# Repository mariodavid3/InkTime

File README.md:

# David Adrian-Mario

## Overview

Acest proiect consta intr-un dispozitiv embedded portabil bazat pe **nRF52840**, capabil sa controleze un display **E-Paper**, sa colecteze date de la un **IMU**, sa ofere feedback prin **haptic driver**, si sa functioneze autonom pe baterie Li-Po.

Dispozitivul include:

* alimentare Li-Po + incarcare USB-C
* conversie DC/DC
* control display e-paper
* senzor IMU
* fuel gauge pentru baterie
* interfata utilizator (butoane + vibratii)
* debugging prin SWD

---
## Materiale

## Block Diagram

## Functionalitate Hardware

### Alimentare

* Intrare: USB-C (5V)
* incarcare baterie Li-Po prin IC dedicat
* Fuel gauge monitorizeaza:
  
  * tensiune
  * nivel baterie
  * estimare autonomie

### DC/DC

* Conversie de la baterie (~3.7V) la 3.3V stabil
* Alimentare pentru MCU si periferice
* Optimizat pentru consum redus

---

### MCU – nRF52840

Roluri:

* control general sistem
* comunicare I2C/SPI
* control display e-paper
* citire senzori
* BLE (optional)

---

### E-Paper

* Controlat prin SPI
* Necesita:

  * tensiuni multiple generate de circuit dedicat (boost + diode)
* Avantaj:

  * consum foarte mic (doar la refresh)

---

### IMU

* Conectat pe I2C
* Masoara:

  * acceleratie
  * rotatie

---

### Haptic

* Driver dedicat (DRV2605)
* Control prin I2C
* Feedback tactil pentru UI

---

### Butoane

* 3 butoane:

  * UP
  * DOWN
  * ENTER
* Conectate la GPIO
* Pull-up/pull-down hardware

---
### USB + ESD

* USB-C pentru alimentare
* Protectie ESD pentru:

  * D+
  * D-
  * VBUS

---

### SWD

* Interfata debugging:

  * SWDIO
  * SWCLK
  * RESET

---

## Mapare pini nRF52840

| Functie        | Pin MCU | Motiv                |
| -------------- | ------- | -------------------- |
| SPI E-Paper    | P0.x    | viteza mare necesara |
| I2C IMU        | P0.x    | standard I2C         |
| I2C Fuel Gauge | P0.x    | bus comun            |
| I2C Haptic     | P0.x    | bus comun            |
| Buttons        | P0.x    | GPIO simplu          |
| SWDIO          | dedicat | debugging            |
| SWCLK          | dedicat | debugging            |
| RESET          | dedicat | control              |

**Motivatie design:**

* I2C shared → reduce pini
* SPI separat → performanta display
* GPIO dedicate → simplitate

---

## Consum de energie (estimare)

| Modul           | Consum           |
| --------------- | ---------------- |
| MCU activ       | ~5-10 mA         |
| MCU sleep       | <10 µA           |
| E-paper refresh | 20-50 mA (scurt) |
| IMU             | ~1-3 mA          |
| Haptic          | ~100 mA (peak)   |

### Optimizari:

* sleep mode agresiv
* e-paper doar la update
* oprire periferice nefolosite

---

## Design PCB

### Observatii:

* Layout compact, dens
* Separare:

  * analog (power)
  * digital (MCU)
* Ground plane continuu
* Trasee scurte pentru:

  * SPI
  * I2C

### Consideratii:

* decuplare langa fiecare IC
* trasee groase pentru power
* protectie ESD langa conector

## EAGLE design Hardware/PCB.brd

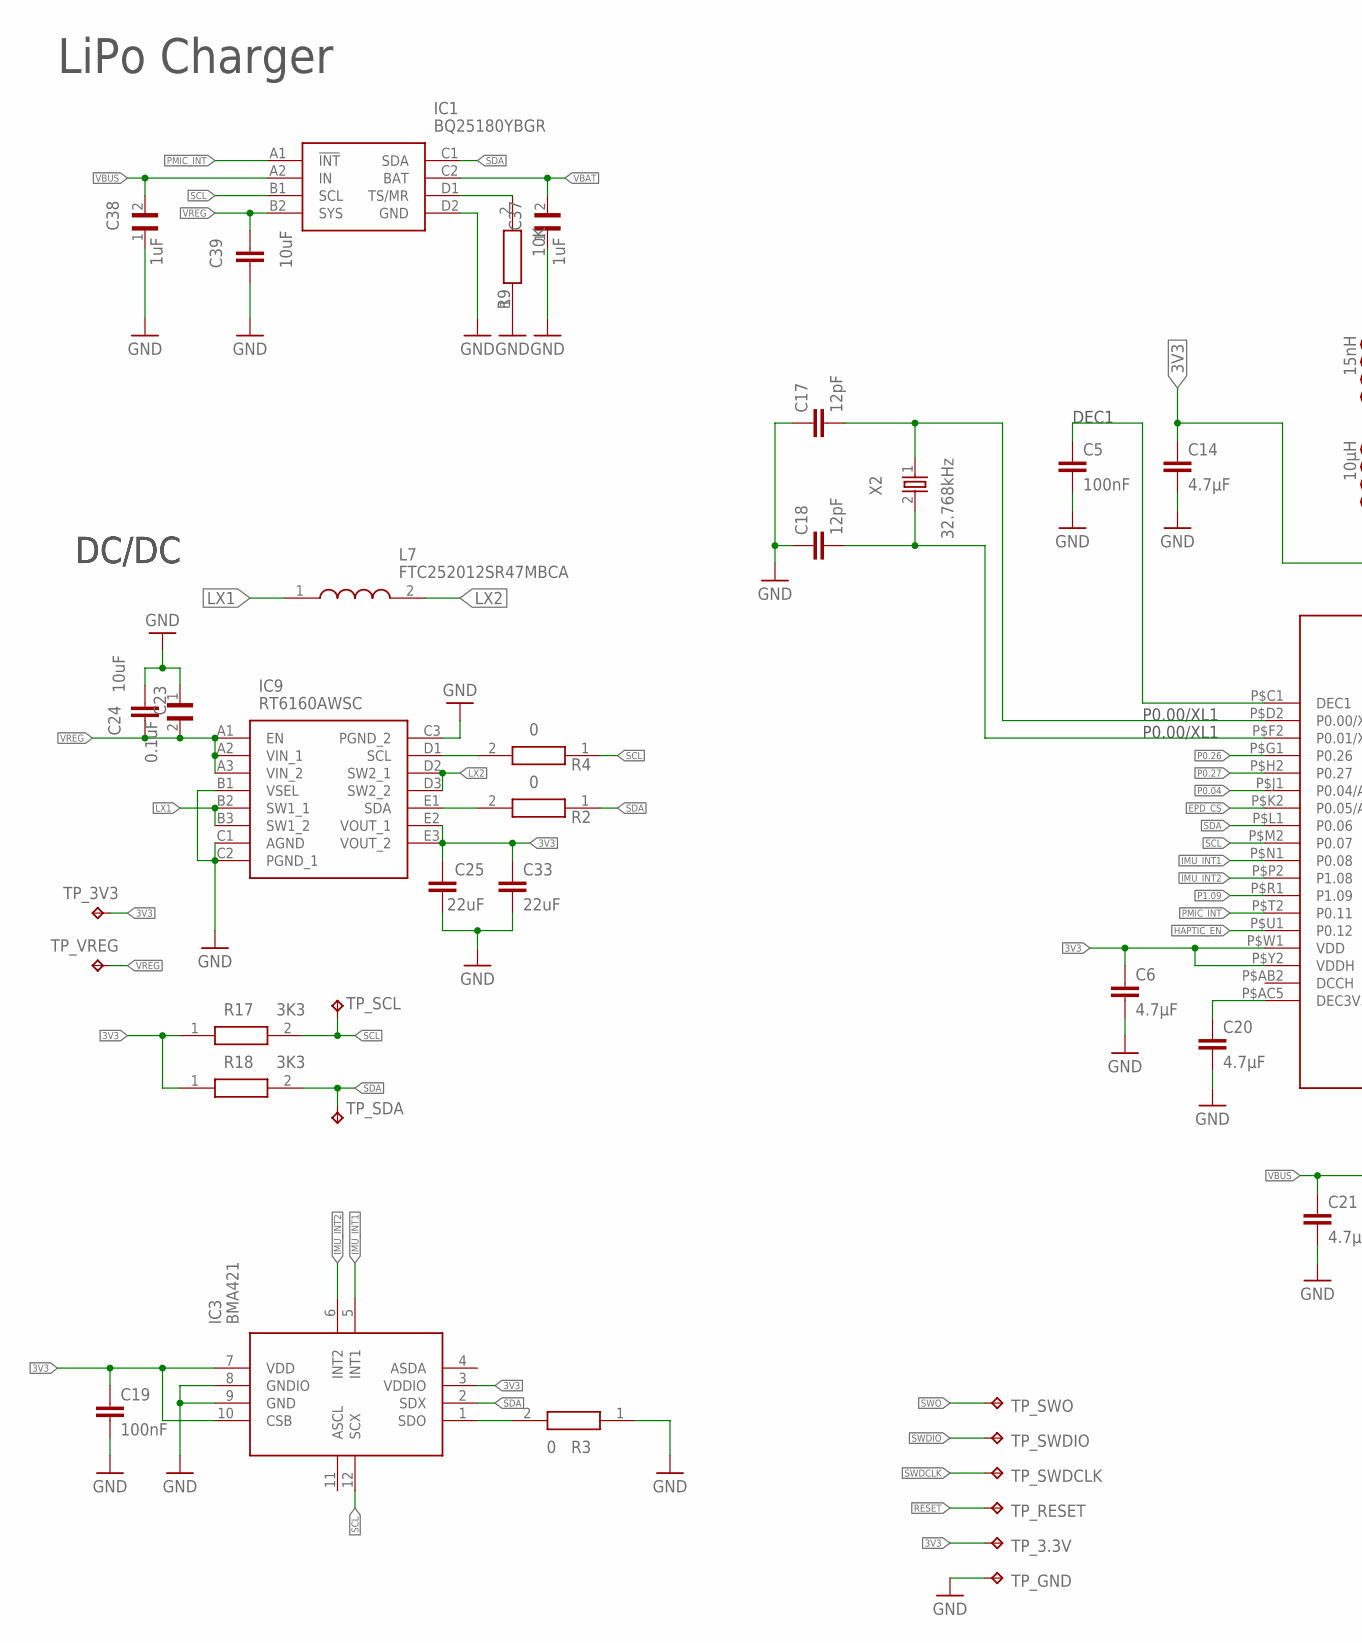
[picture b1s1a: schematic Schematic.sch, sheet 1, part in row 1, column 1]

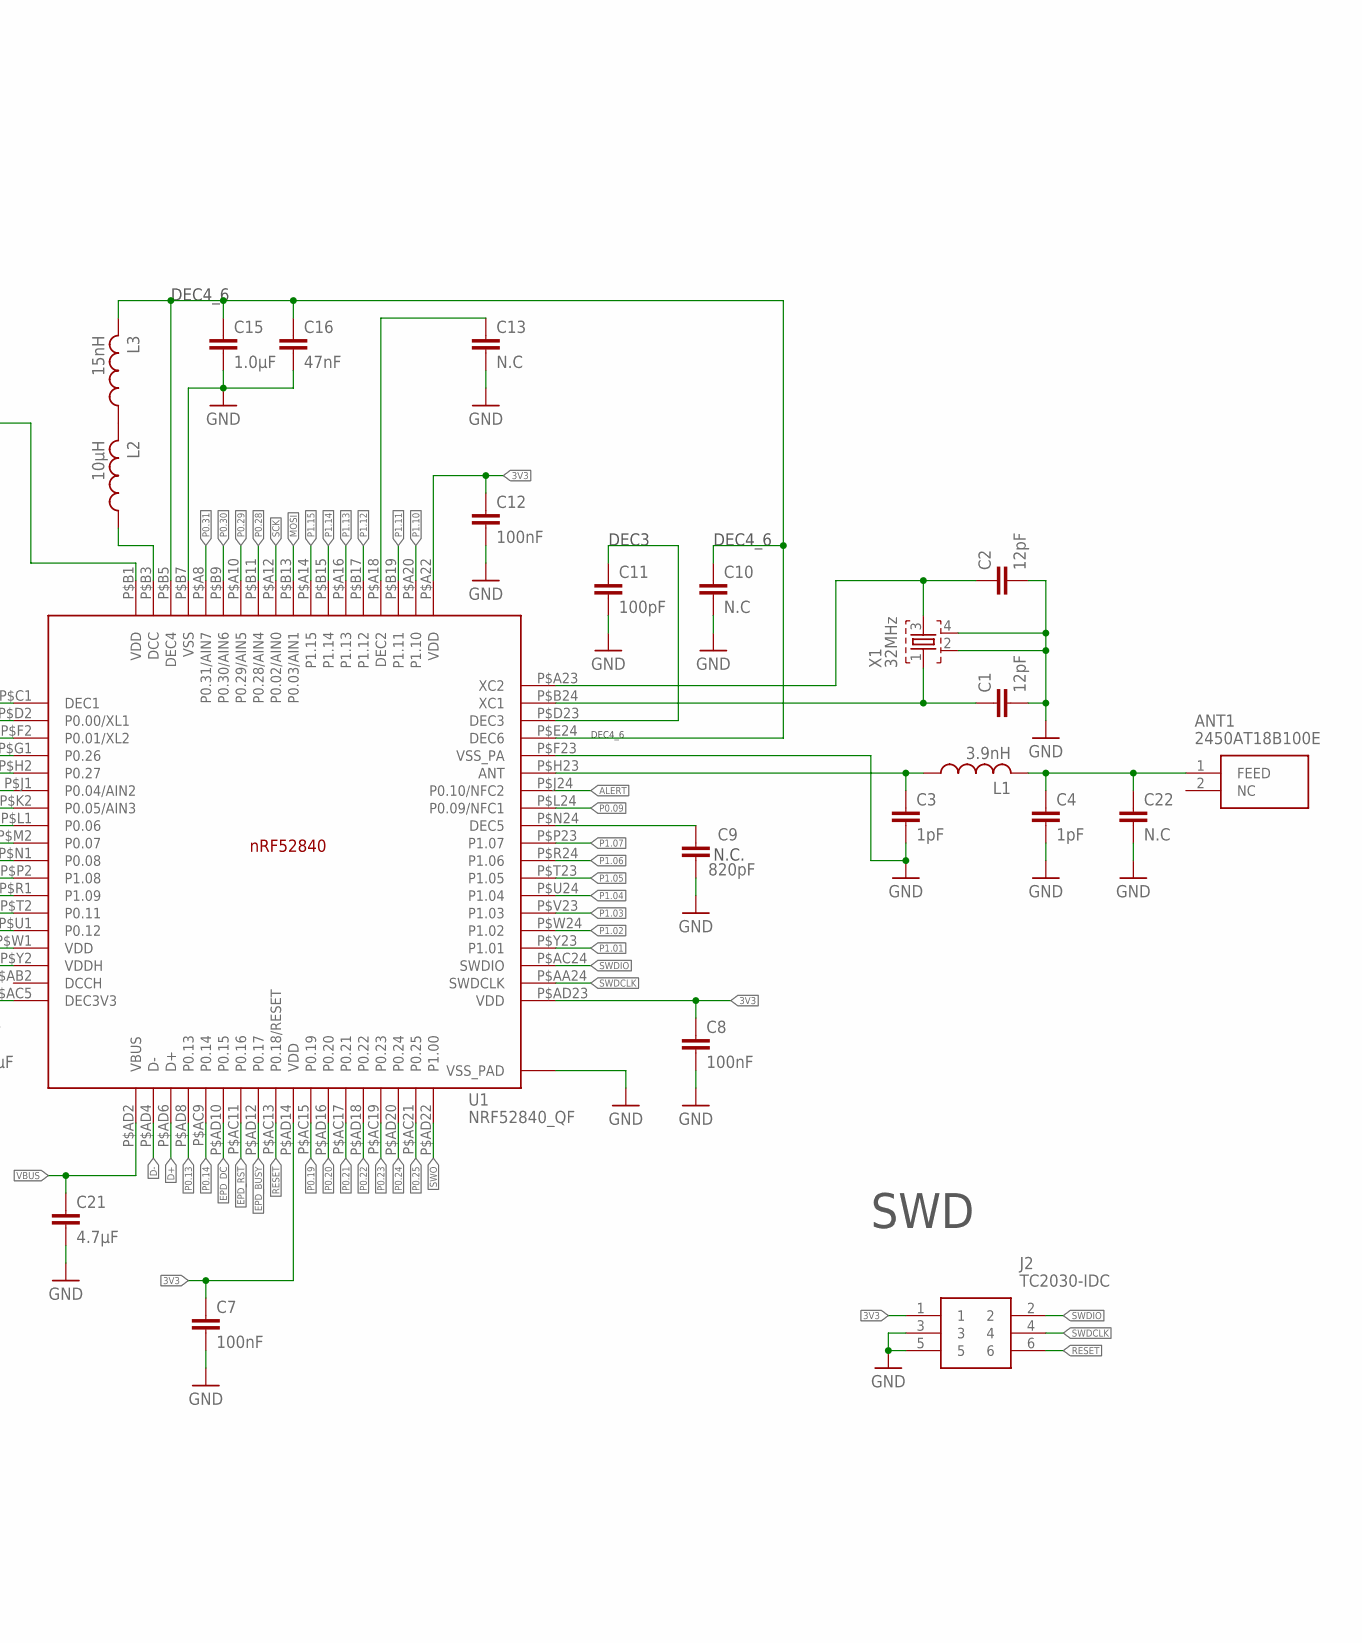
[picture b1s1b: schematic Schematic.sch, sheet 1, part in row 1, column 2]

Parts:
ANT1: 2450AT18B100E; 2450AT18B100E_ANTC3216X140N
C1, C2, C17, C18: 12pF; NORDIC_NRF_3_RESC0201_L
C3, C4: 1pF; NORDIC_NRF_3_RESC0201_L
C5, C7, C8, C12, C19: 100nF; NORDIC_NRF_3_RESC0201_L
C6, C14, C20, C21: 4.7µF; PERFECT_0402_0402
C9: 820pF; NORDIC_NRF_3_RESC0201_L
C10, C13, C22: N.C; NORDIC_NRF_3_RESC0201_L
C11: 100pF; NORDIC_NRF_3_RESC0201_L
C15: 1.0µF; PERFECT_0402_0402
C16: 47nF; NORDIC_NRF_3_RESC0201_L
C23: 0.1uF; GRM011R60J152KE01L_2_CAPC0201X13N
C24, C39: 10uF; PERFECT_0402_0402
C25, C33: 22uF; PERFECT_0402_0402
C37, C38: 1uF; GRM011R60J152KE01L_2_CAPC0201X13N
IC1: BQ25180YBGR; BQ25180YBGR_BGA8C40P2X4_100X155X50
IC3: BMA421; BMA423_BMA423
IC9: RT6160AWSC; RT6160AWSC_BGA15C40P3X5_140X230X60
J2: TC2030-IDC; TC2030-IDC_TC2030IDC
L1: 3.9nH; NORDIC_NRF_2_RESC0402_L
L2: 10µH; NORDIC_NRF_2_RESC0402_L
L3: 15nH; NORDIC_NRF_2_RESC0402_L
L7: FTC252012SR47MBCA; MLP2016SR47MT0S1_INDC2016X100N
R2, R3, R4: 0; CPF0201D7K68C1_0201
R9: 10K; CPF0201D7K68C1_0201
R17, R18: 3K3; CPF0201D7K68C1_0201
TP_3.3V, TP_3V3: HECTOR_WATCH_1_TPTP20R; HECTOR_WATCH_1_TP20R
TP_GND: HECTOR_WATCH_1_TPTP20R; HECTOR_WATCH_1_TP20R
TP_RESET: HECTOR_WATCH_1_TPTP20R; HECTOR_WATCH_1_TP20R
TP_SCL: HECTOR_WATCH_1_TPTP20R; HECTOR_WATCH_1_TP20R
TP_SDA: HECTOR_WATCH_1_TPTP20R; HECTOR_WATCH_1_TP20R
TP_SWDCLK: HECTOR_WATCH_1_TPTP20R; HECTOR_WATCH_1_TP20R
TP_SWDIO: HECTOR_WATCH_1_TPTP20R; HECTOR_WATCH_1_TP20R
TP_SWO: HECTOR_WATCH_1_TPTP20R; HECTOR_WATCH_1_TP20R
TP_VREG: HECTOR_WATCH_1_TPTP20R; HECTOR_WATCH_1_TP20R
U1: NRF52840_QF; NORDIC_NRF_4_AQFN50P700X700X85_HS-74N
X1: 32MHz; NORDIC_NRF_BT-XTAL_2016_N
X2: 32.768kHz; NORDIC_NRF_1_XTAL_3215_N

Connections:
3V3: C6.1, C7.1, C8.1, C12.1, C14.1, C19.1, C25.2, C33.1, IC3.3 (VDDIO), IC3.7 (VDD), IC3.10 (CSB), IC9.E2 (VOUT_1), IC9.E3 (VOUT_2), J2.1, R17.1, R18.1, TP_3.3V.TP, TP_3V3.TP, U1.P$A22 (VDD), U1.P$AD14 (VDD), U1.P$AD23 (VDD), U1.P$B1 (VDD), U1.P$W1 (VDD), U1.P$Y2 (VDDH); also elsewhere on the board
ALERT: U1.P$J24 (P0.10/NFC2); also elsewhere on the board
D+: U1.P$AD6 (D+); also elsewhere on the board
D-: U1.P$AD4 (D-); also elsewhere on the board
EPD_BUSY: U1.P$AD12 (P0.17); also elsewhere on the board
EPD_CS: U1.P$K2 (P0.05/AIN3); also elsewhere on the board
EPD_DC: U1.P$AD10 (P0.15); also elsewhere on the board
EPD_RST: U1.P$AC11 (P0.16); also elsewhere on the board
GND: C1.2, C2.2, C3.2, C4.2, C5.2, C6.2, C7.2, C8.2, C9.1, C10.2, C11.2, C12.2, C13.2, C14.2, C15.2, C16.2, C17.1, C18.1, C19.2, C20.2, C21.2, C22.2, C23.1, C24.1, C25.1, C33.2, C37.1, C38.1, C39.1, IC1.D2 (GND), IC3.8 (GNDIO), IC3.9 (GND), IC9.B1 (VSEL), IC9.C1 (AGND), IC9.C2 (PGND_1), IC9.C3 (PGND_2), J2.3, J2.5, R3.1, R9.1, TP_GND.TP, U1.P$74 (VSS_PAD), U1.P$75 (VSS_PAD), U1.P$76 (VSS_PAD), U1.P$77 (VSS_PAD), U1.P$78 (VSS_PAD), U1.P$79 (VSS_PAD), U1.P$80 (VSS_PAD), U1.P$81 (VSS_PAD), U1.P$82 (VSS_PAD), U1.P$83 (VSS_PAD), U1.P$84 (VSS_PAD), U1.P$85 (VSS_PAD), U1.P$86 (VSS_PAD), U1.P$87 (VSS_PAD), U1.P$88 (VSS_PAD), U1.P$89 (VSS_PAD), U1.P$90 (VSS_PAD), U1.P$B7 (VSS), U1.P$F23 (VSS_PA), X1.2, X1.4; also elsewhere on the board
HAPTIC_EN: U1.P$U1 (P0.12); also elsewhere on the board
IMU_INT1: IC3.5 (INT1), U1.P$N1 (P0.08)
IMU_INT2: IC3.6 (INT2), U1.P$P2 (P1.08)
LX1: IC9.B2 (SW1_1), IC9.B3 (SW1_2), L7.1
LX2: IC9.D2 (SW2_1), IC9.D3 (SW2_2), L7.2
MOSI: U1.P$B13 (P0.03/AIN1); also elsewhere on the board
unnamed: IC1.D1 (TS/MR), R9.2
unnamed: IC3.1 (SDO), R3.2
unnamed: IC9.D1 (SCL), R4.2
unnamed: C9.2, U1.P$N24 (DEC5)
unnamed: IC9.E1 (SDA), R2.2
unnamed: C20.1, U1.P$AC5 (DEC3V3)
unnamed: C13.1, U1.P$A18 (DEC2)
unnamed: C11.1, U1.P$D23 (DEC3)
unnamed: L2.1, U1.P$B3 (DCC)
unnamed: L2.2, L3.1
unnamed: C10.1, C15.1, C16.1, L3.2, U1.P$B5 (DEC4), U1.P$E24 (DEC6)
unnamed: C2.1, U1.P$A23 (XC2), X1.3
unnamed: C1.1, U1.P$B24 (XC1), X1.1
unnamed: C3.1, L1.1, U1.P$H23 (ANT)
unnamed: ANT1.1 (FEED), C4.1, C22.1, L1.2
unnamed: C18.2, U1.P$F2 (P0.01/XL2), X2.2
unnamed: C17.2, U1.P$D2 (P0.00/XL1), X2.1
unnamed: C5.1, U1.P$C1 (DEC1)
P0.04: U1.P$J1 (P0.04/AIN2)
P0.09: U1.P$L24 (P0.09/NFC1)
P0.13: U1.P$AD8 (P0.13); also elsewhere on the board
P0.14: U1.P$AC9 (P0.14); also elsewhere on the board
P0.19: U1.P$AC15 (P0.19)
P0.20: U1.P$AD16 (P0.20)
P0.21: U1.P$AC17 (P0.21)
P0.22: U1.P$AD18 (P0.22)
P0.23: U1.P$AC19 (P0.23)
P0.24: U1.P$AD20 (P0.24)
P0.25: U1.P$AC21 (P0.25)
P0.26: U1.P$G1 (P0.26)
P0.27: U1.P$H2 (P0.27)
P0.28: U1.P$B11 (P0.28/AIN4)
P0.29: U1.P$A10 (P0.29/AIN5)
P0.30: U1.P$B9 (P0.30/AIN6)
P0.31: U1.P$A8 (P0.31/AIN7)
P1.01: U1.P$Y23 (P1.01); also elsewhere on the board
P1.02: U1.P$W24 (P1.02); also elsewhere on the board
P1.03: U1.P$V23 (P1.03)
P1.04: U1.P$U24 (P1.04)
P1.05: U1.P$T23 (P1.05)
P1.06: U1.P$R24 (P1.06)
P1.07: U1.P$P23 (P1.07)
P1.09: U1.P$R1 (P1.09)
P1.10: U1.P$A20 (P1.10)
P1.11: U1.P$B19 (P1.11)
P1.12: U1.P$B17 (P1.12)
P1.13: U1.P$A16 (P1.13)
P1.14: U1.P$B15 (P1.14)
P1.15: U1.P$A14 (P1.15)
PMIC_INT: IC1.A1 (!INT), U1.P$T2 (P0.11)
RESET: J2.6, TP_RESET.TP, U1.P$AC13 (P0.18/RESET)
SCK: U1.P$A12 (P0.02/AIN0); also elsewhere on the board
SCL: IC1.B1 (SCL), IC3.12 (SCX), R4.1, R17.2, TP_SCL.TP, U1.P$M2 (P0.07); also elsewhere on the board
SDA: IC1.C1 (SDA), IC3.2 (SDX), R2.1, R18.2, TP_SDA.TP, U1.P$L1 (P0.06); also elsewhere on the board
SWDCLK: J2.4, TP_SWDCLK.TP, U1.P$AA24 (SWDCLK)
SWDIO: J2.2, TP_SWDIO.TP, U1.P$AC24 (SWDIO)
SWO: TP_SWO.TP, U1.P$AD22 (P1.00)
VBAT: C37.2, IC1.C2 (BAT); also elsewhere on the board
VBUS: C21.1, C38.2, IC1.A2 (IN), U1.P$AD2 (VBUS); also elsewhere on the board
VREG: C23.2, C24.2, C39.2, IC1.B2 (SYS), IC9.A1 (EN), IC9.A2 (VIN_1), IC9.A3 (VIN_2), TP_VREG.TP

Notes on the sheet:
LiPo Charger
DC/DC
SWD
P0.00/XL1
DEC4_6
DEC1
DEC3
N.C.

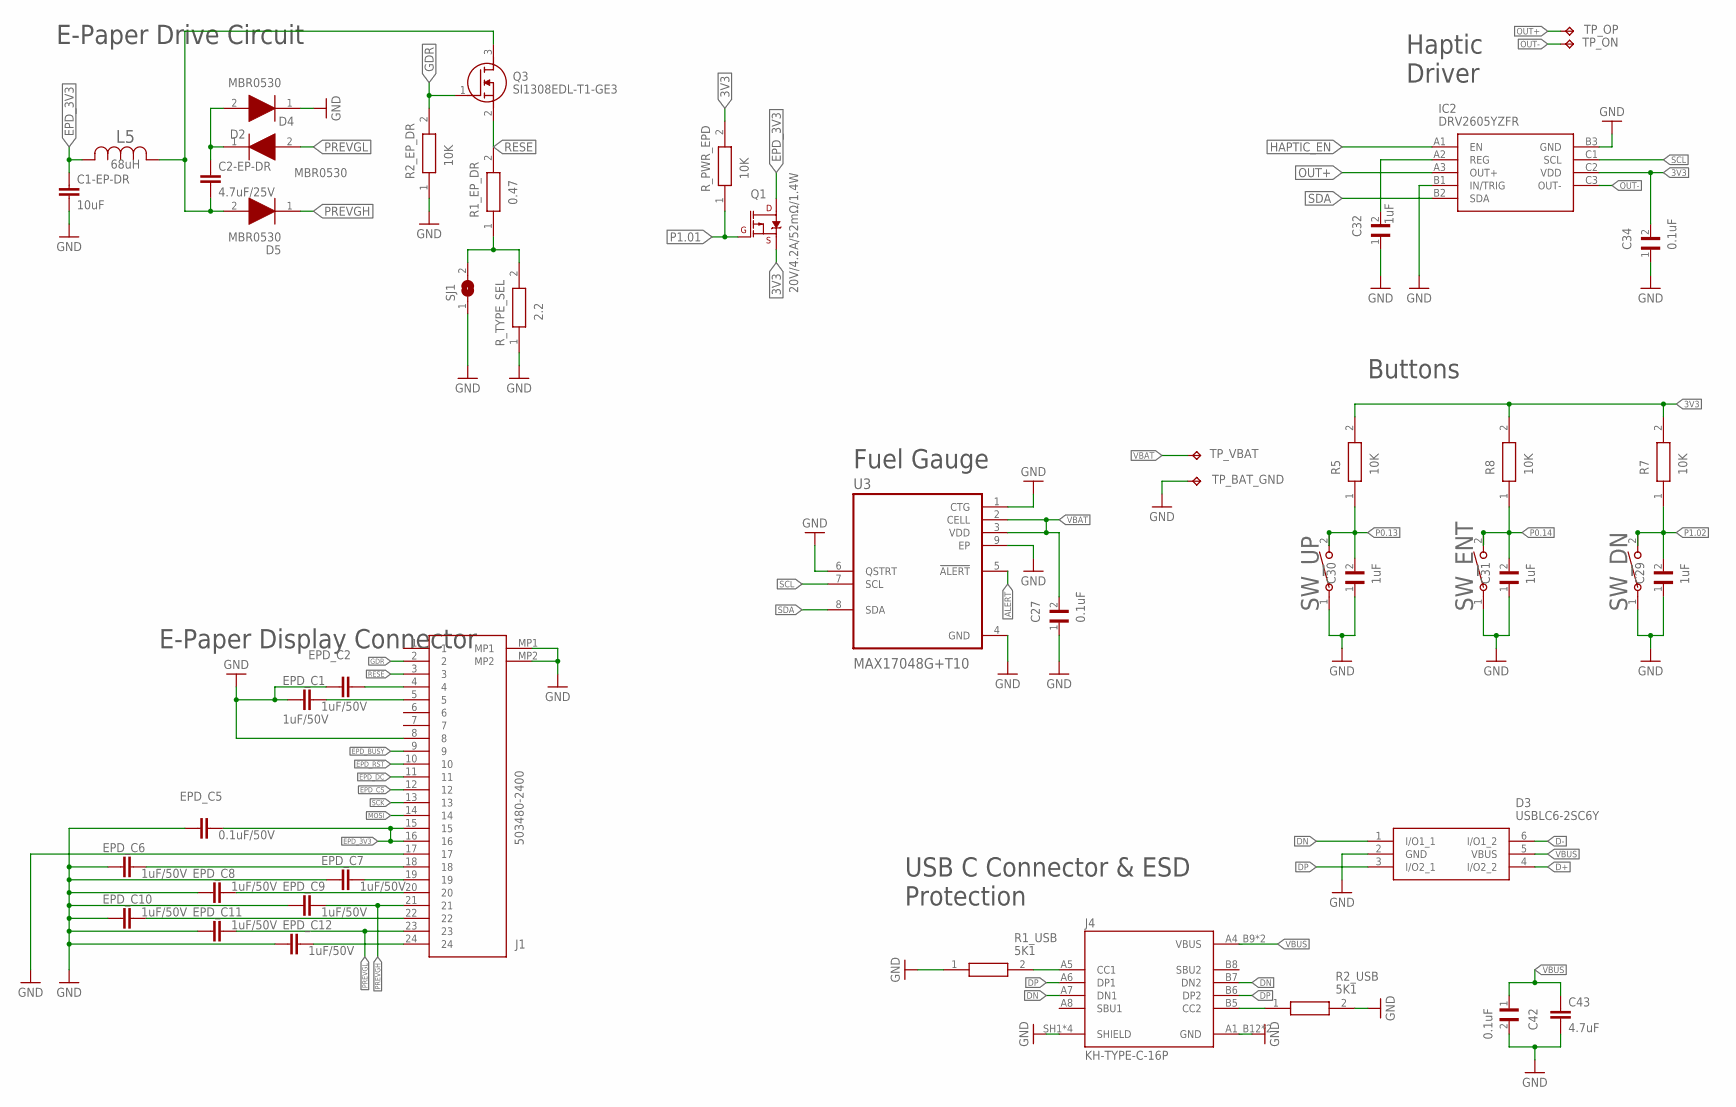
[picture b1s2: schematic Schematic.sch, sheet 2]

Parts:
C1-EP-DR: 10uF; NORDIC_NRF_3_RESC0603_L
C2-EP-DR: 4.7uF/25V; NORDIC_NRF_3_RESC0603_L
C27, C34, C42: 0.1uF; GRM011R60J152KE01L_2_CAPC0201X13N
C29, C30, C31, C32: 1uF; GRM011R60J152KE01L_2_CAPC0201X13N
C43: 4.7uF; PERFECT_0402_0402
D2, D4, D5: MBR0530; ESP32_C6_LIBRARY_5_SOD3716X135N
D3: USBLC6-2SC6Y; ESP32_C6_LIBRARY_3_SOT95P280X145-6N
EPD_C1, EPD_C2, EPD_C6, EPD_C7, EPD_C8, EPD_C9, EPD_C10, EPD_C11, EPD_C12: 1uF/50V; PERFECT_0402_0402
EPD_C5: 0.1uF/50V; NORDIC_NRF_3_RESC0201_L
IC2: DRV2605YZFR; DRV2605YZFR_BGA9C50P3X3_144X144X62
J1: 503480-2400; 503480-2400_5034802400
J4: KH-TYPE-C-16P; KH-TYPE-C-16P_KINGHELM_KH-TYPE-C-16P
L5: 68uH; ESP32_C6_LIBRARY_2_IND_4828-WE-TPC_WRE
Q1: 20V/4.2A/52mΩ/1.4W; ESP32_C6_LIBRARY_4_ESP32_C6_LIBRARY_4_ESP32_C6_LIBRARY_4_ES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
Q3: SI1308EDL-T1-GE3; ESP32_C6_LIBRARY_6_SOT65P210X110-3N
R1_EP_DR: 0.47; CPF0201D7K68C1_0201
R1_USB, R2_USB: 5K1; CPF0201D7K68C1_0201
R2_EP_DR, R5, R7, R8: 10K; CPF0201D7K68C1_0201
R_PWR_EPD: 10K; CPF0201D7K68C1_0201
R_TYPE_SEL: 2.2; CPF0201D7K68C1_0201
SJ1: ESP32_C6_LIBRARY_7_JUMPER_SJ
SW_DN: 2025-10-22_07-23-44_LIBRARY_EVP-AKE31ASW_EVP-AKE3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; 2025-10-22_07-23-44_LIBRARY_SW_EVP-AKE31A_PAN
SW_ENT: 2025-10-22_07-23-44_LIBRARY_EVP-AKE31ASW_EVP-AKE3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; 2025-10-22_07-23-44_LIBRARY_SW_EVP-AKE31A_PAN
SW_UP: 2025-10-22_07-23-44_LIBRARY_EVP-AKE31ASW_EVP-AKE3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; 2025-10-22_07-23-44_LIBRARY_SW_EVP-AKE31A_PAN
TP_BAT_GND: HECTOR_WATCH_1_TPTP20R; HECTOR_WATCH_1_TP20R
TP_ON: HECTOR_WATCH_1_TPTP20R; HECTOR_WATCH_1_TP20R
TP_OP: HECTOR_WATCH_1_TPTP20R; HECTOR_WATCH_1_TP20R
TP_VBAT: HECTOR_WATCH_1_TPTP20R; HECTOR_WATCH_1_TP20R
U3: MAX17048G+T10; ESP32_C6_LIBRARY_SON50P200X200X80-9N

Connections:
3V3: C34.2, IC2.C2 (VDD), Q1.2 (S), R5.2, R7.2, R8.2, R_PWR_EPD.2; also elsewhere on the board
ALERT: U3.5 (!ALERT); also elsewhere on the board
D+: D3.4 (I/O2_2); also elsewhere on the board
D-: D3.6 (I/O1_2); also elsewhere on the board
DN: D3.1 (I/O1_1), J4.A7 (DN1), J4.B7 (DN2)
DP: D3.3 (I/O2_1), J4.A6 (DP1), J4.B6 (DP2)
EPD_3V3: C1-EP-DR.1, EPD_C5.1, J1.15, J1.16, L5.2, Q1.3 (D)
EPD_BUSY: J1.9; also elsewhere on the board
EPD_CS: J1.12; also elsewhere on the board
EPD_DC: J1.11; also elsewhere on the board
EPD_RST: J1.10; also elsewhere on the board
GDR: J1.2, Q3.1 (G), R2_EP_DR.2
GND: C1-EP-DR.2, C27.1, C29.1, C30.1, C31.1, C32.1, C34.1, C42.2, C43.2, D3.2 (GND), D4.1 (K), EPD_C1.2, EPD_C2.2, EPD_C5.2, EPD_C6.2, EPD_C7.2, EPD_C8.2, EPD_C9.2, EPD_C10.2, EPD_C11.2, EPD_C12.2, IC2.B1 (IN/TRIG), IC2.B3 (GND), J1.8, J1.17, J1.MP1, J1.MP2, J4.A1_B12 (GND), J4.A12_B1 (GND), J4.SH1 (SHIELD), J4.SH2 (SHIELD), J4.SH3 (SHIELD), J4.SH4 (SHIELD), R1_USB.1, R2_EP_DR.1, R2_USB.2, R_TYPE_SEL.1, SJ1.1, SW_DN.1, SW_ENT.1, SW_UP.1, TP_BAT_GND.TP, U3.1 (CTG), U3.4 (GND), U3.6 (QSTRT), U3.9 (EP); also elsewhere on the board
HAPTIC_EN: IC2.A1 (EN); also elsewhere on the board
MOSI: J1.14; also elsewhere on the board
unnamed: EPD_C6.1, J1.18
unnamed: C2-EP-DR.2, D5.2 (A), L5.1, Q3.3 (D)
unnamed: C2-EP-DR.1, D2.1 (K), D4.2 (A)
unnamed: R1_EP_DR.1, R_TYPE_SEL.2, SJ1.2
unnamed: J4.B5 (CC2), R2_USB.1
unnamed: EPD_C7.1, J1.19
unnamed: C32.2, IC2.A2 (REG)
unnamed: EPD_C2.1, J1.4
unnamed: EPD_C1.1, J1.5
unnamed: J4.A5 (CC1), R1_USB.2
unnamed: EPD_C8.1, J1.20
unnamed: EPD_C10.1, J1.22
unnamed: EPD_C12.1, J1.24
OUT+: IC2.A3 (OUT+), TP_OP.TP
OUT-: IC2.C3 (OUT-), TP_ON.TP
P0.13: C30.2, R5.1, SW_UP.2; also elsewhere on the board
P0.14: C31.2, R8.1, SW_ENT.2; also elsewhere on the board
P1.01: Q1.1 (G), R_PWR_EPD.1; also elsewhere on the board
P1.02: C29.2, R7.1, SW_DN.2; also elsewhere on the board
PREVGH: D5.1 (K), EPD_C9.1, J1.21
PREVGL: D2.2 (A), EPD_C11.1, J1.23
RESE: J1.3, Q3.2 (S), R1_EP_DR.2
SCK: J1.13; also elsewhere on the board
SCL: IC2.C1 (SCL), U3.7 (SCL); also elsewhere on the board
SDA: IC2.B2 (SDA), U3.8 (SDA); also elsewhere on the board
VBAT: C27.2, TP_VBAT.TP, U3.2 (CELL), U3.3 (VDD); also elsewhere on the board
VBUS: C42.1, C43.1, D3.5 (VBUS), J4.A4_B9 (VBUS), J4.A9_B4 (VBUS); also elsewhere on the board

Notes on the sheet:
E-Paper Drive Circuit
Haptic Driver
Buttons
Fuel Gauge
USB C Connector & ESD Protection
E-Paper Display Connector

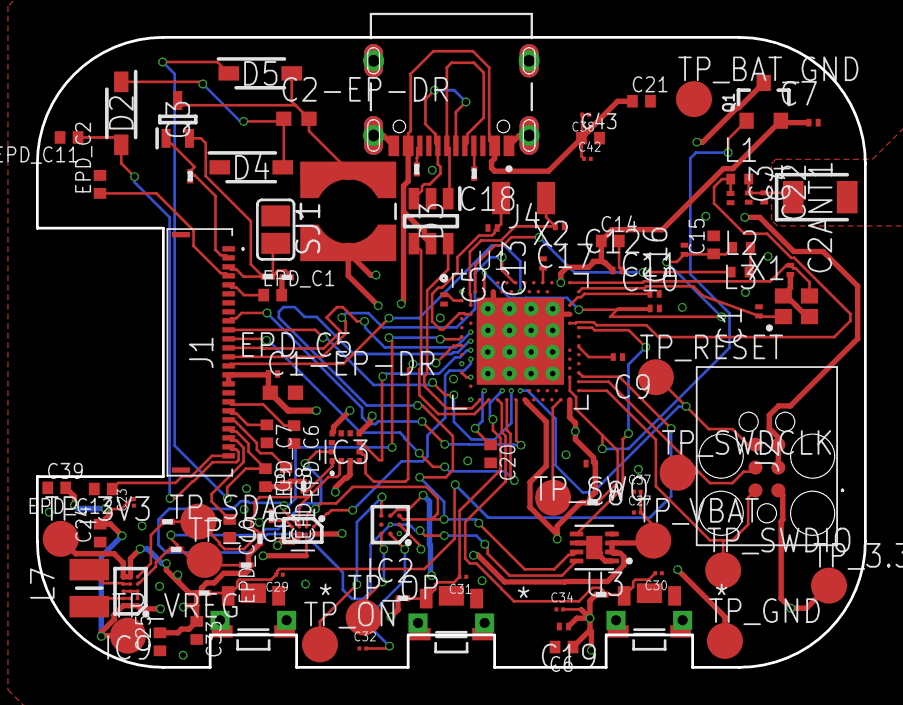
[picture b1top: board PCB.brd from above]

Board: 4 copper layers, 46.0 x 35.0 mm, 105 parts (0 on the bottom side), 70 nets.

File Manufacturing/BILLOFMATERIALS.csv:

Reference Designators;Quantity;Description;Package;Value;Manufacturer;Manufacturer Part Number;Vendor;Vendor Part Number;Top/Bottom;
;1;PCB Board;Board;;;;;;;
ANT1;1;Antennas 2.45GHz ANTENNA;2450AT18B100E_ANTC3216X140N;2450AT18B100E;;;;;Top;
C1, C2, C17, C18;4;Generic chip capacitor;NORDIC_NRF_3_RESC0201_L;12pF;;;;;Top;
C1-EP-DR;1;Generic chip capacitor;NORDIC_NRF_3_RESC0603_L;10uF;;;;;Top;
C2-EP-DR;1;Generic chip capacitor;NORDIC_NRF_3_RESC0603_L;4.7uF/25V;;;;;Top;
C3, C4;2;Generic chip capacitor;NORDIC_NRF_3_RESC0201_L;1pF;;;;;Top;
C5, C7, C8, C12, C19;5;Generic chip capacitor;NORDIC_NRF_3_RESC0201_L;100nF;;;;;Top;
C6, C14, C20, C21;4;0402 (1005 Metric);PERFECT_0402_0402;4.7µF;;;;;Top;
C9;1;Generic chip capacitor;NORDIC_NRF_3_RESC0201_L;820pF;;;;;Top;
C10, C13, C22;3;Generic chip capacitor;NORDIC_NRF_3_RESC0201_L;N.C;;;;;Top;
C11;1;Generic chip capacitor;NORDIC_NRF_3_RESC0201_L;100pF;;;;;Top;
C15;1;0402 (1005 Metric);PERFECT_0402_0402;1.0µF;;;;;Top;
C16;1;Generic chip capacitor;NORDIC_NRF_3_RESC0201_L;47nF;;;;;Top;
C23, C27, C34, C42;4;Check availability;CAPC0201X13N;0.1uF;;;;;Top;
C24, C39;2;0402 (1005 Metric);PERFECT_0402_0402;10uF;;;;;Top;
C25, C33;2;0402 (1005 Metric);PERFECT_0402_0402;22uF;;;;;Top;
C29, C30, C31, C32, C37, C38;6;Check availability;CAPC0201X13N;1uF;;;;;Top;
C43;1;0402 (1005 Metric);PERFECT_0402_0402;4.7uF;;;;;Top;
D2, D4, D5;3;ON SEMICONDUCTOR - MBR0530 - DIODE, SCHOTTKY, 0.5A, 30V, SOD-123;SOD3716X135N;MBR0530;;;;;Top;
D3;1;Low Cap. ESD Protection Auto SOT-23-6 STMicroelectronics USBLC6-2SC6Y, Dual Uni-Directional TVS Diode Array, 6-Pin SOT-23;SOT95P280X145-6N;USBLC6-2SC6Y;;;;;Top;
EPD_C1, EPD_C2, EPD_C6, EPD_C7, EPD_C8, EPD_C9, EPD_C10, EPD_C11, EPD_C12;9;0402 (1005 Metric);PERFECT_0402_0402;1uF/50V;;;;;Top;
EPD_C5;1;Generic chip capacitor;NORDIC_NRF_3_RESC0201_L;0.1uF/50V;;;;;Top;
IC1;1;Charger IC Lithium Ion/Polymer, Lithium Iron Phosphate 8-DSBGA (1.6x1.1);BQ25180YBGR_BGA8C40P2X4_100X155X50;BQ25180YBGR;;;;;Top;
IC2;1;Haptic Driver for ERM/LRA with Built-In Library and Smart Loop Architecture;DRV2605YZFR_BGA9C50P3X3_144X144X62;DRV2605YZFR;;;;;Top;
IC3;1;Accelerometers Triaxial low-g 12bit Acceleration Sensor;BMA423_BMA423;BMA421;;;;;Top;
IC9;1;Buck-Boost Regulator Positive Output Step-Up/Step-Down I2C DC-DC Controller IC 15-WL-CSP (BSC) (1.4x2.3);RT6160AWSC_BGA15C40P3X5_140X230X60;RT6160AWSC;;;;;Top;
J1;1;FFC & FPC Connectors 0.5mm FPC RA SMT Dual Contact 24Ckt;503480-2400_5034802400;503480-2400;;;;;Top;
J2;1;CABLE ADAPTER 6 POS;TC2030-IDC_TC2030IDC;TC2030-IDC;;;;;Top;
J4;1;Check availability;KINGHELM_KH-TYPE-C-16P;KH-TYPE-C-16P;;;;;Top;
L1;1;Generic chip inductor;NORDIC_NRF_2_RESC0402_L;3.9nH;;;;;Top;
L2;1;Generic chip inductor;NORDIC_NRF_2_RESC0402_L;10µH;;;;;Top;
L3;1;Generic chip inductor;NORDIC_NRF_2_RESC0402_L;15nH;;;;;Top;
L5;1;;ESP32_C6_LIBRARY_2_IND_4828-WE-TPC_WRE;68uH;;;;;Top;
L7;1;SMD / SMT Inductors (Coils), L=0.47?H, L x W x T :;MLP2016SR47MT0S1_INDC2016X100N;FTC252012SR47MBCA;;;;;Top;
Q1;1;P-channel MOSFETs;ESP32_WROVER_SPARKFUN-DISCRETESEMI_SOT23-3;20V/4.2A/52mΩ/1.4W;;;;;Top;
Q3;1;MOSFET N-Ch 30V 1.5A TrenchFET SC70 Vishay Si1308EDL-T1-GE3 N-channel MOSFET Transistor, 1.5 A, 30 V, 3-Pin SC-70;SOT65P210X110-3N;SI1308EDL-T1-GE3;;;;;Top;
R_PWR_EPD, R2_EP_DR, R5, R7, R8, R9;6;7.68k 0201 Thin Film Surface Mount Fixed Resistor +/-0.5% 0.031W CPF0201D7K68C1;CPF0201D7K68C1_0201;10K;;;;;Top;
R_TYPE_SEL;1;7.68k 0201 Thin Film Surface Mount Fixed Resistor +/-0.5% 0.031W CPF0201D7K68C1;CPF0201D7K68C1_0201;2.2;;;;;Top;
R1_EP_DR;1;7.68k 0201 Thin Film Surface Mount Fixed Resistor +/-0.5% 0.031W CPF0201D7K68C1;CPF0201D7K68C1_0201;0.47;;;;;Top;
R1_USB, R2_USB;2;7.68k 0201 Thin Film Surface Mount Fixed Resistor +/-0.5% 0.031W CPF0201D7K68C1;CPF0201D7K68C1_0201;5K1;;;;;Top;
R2, R3, R4;3;7.68k 0201 Thin Film Surface Mount Fixed Resistor +/-0.5% 0.031W CPF0201D7K68C1;CPF0201D7K68C1_0201;0;;;;;Top;
R17, R18;2;7.68k 0201 Thin Film Surface Mount Fixed Resistor +/-0.5% 0.031W CPF0201D7K68C1;CPF0201D7K68C1_0201;3K3;;;;;Top;
SJ1;1;SMD solder JUMPER;JUMPER_SJ;;;;;;Top;
SW_DN, SW_ENT, SW_UP;3;;SW_EVP-AKE31A_PAN;2025-10-22_07-23-44_LIBRARY_EVP-AKE31ASW_EVP-AKE31A_PAN;;;;;Top;
TP_3.3V, TP_3V3, TP_BAT_GND, TP_GND, TP_ON, TP_OP, TP_RESET, TP_SCL, TP_SDA, TP_SWDCLK, TP_SWDIO, TP_SWO, TP_VBAT, TP_VREG;14;Test pad;HECTOR_WATCH_1_TP20R;HECTOR_WATCH_1_TPTP20R;;;;;Top;
U1;1;nRF52840;NORDIC_NRF_4_AQFN50P700X700X85_HS-74N;NRF52840_QF;;;;;Top;
U3;1;Check availability;SON50P200X200X80-9N;MAX17048G+T10;;;;;Top;
X1;1;;NORDIC_NRF_BT-XTAL_2016_N;32MHz;;;;;Top;
X2;1;;NORDIC_NRF_1_XTAL_3215_N;32.768kHz;;;;;Top;

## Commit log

2026-04-17 commit 2

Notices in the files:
parts and their libraries:
COPYRIGHT: Copyright (C) 2024 Ultra Librarian. All rights reserved.
COPYRIGHT: Copyright (C) 2025 Ultra Librarian. All rights reserved.
